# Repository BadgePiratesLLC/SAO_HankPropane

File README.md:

# SAO_HankPropane
HankPropane SAO

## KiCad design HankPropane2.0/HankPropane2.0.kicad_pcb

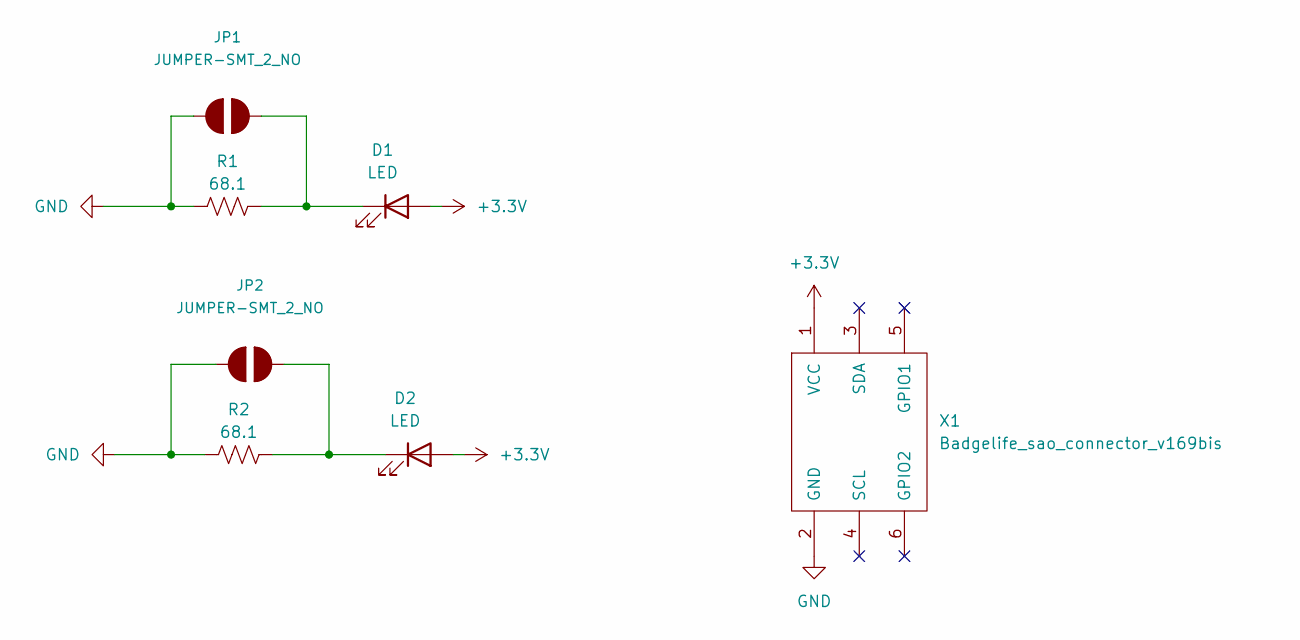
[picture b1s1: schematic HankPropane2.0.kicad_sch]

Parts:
D1, D2: LED; LED_Osram_Lx_P47F_D2mm_ReverseMount_Proper_Mask Only
JP1, JP2: JUMPER-SMT_2_NO; SolderJumper-2_P1.3mm_Open_TrianglePad1.0x1.5mm
R1, R2: 68.1; R_1206_3216Metric_Pad1.30x1.75mm_HandSolder
X1: Badgelife_sao_connector_v169bis; Badgelife-SAOv169-BADGE-2x3_Back

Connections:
+3V3: D1.2 (A), D2.2 (A), X1.1 (VCC)
GND: JP1.1, JP2.1, R1.1, R2.1, X1.2 (GND)
unnamed: D1.1 (K), JP1.2, R1.2
unnamed: D2.1 (K), JP2.2, R2.2

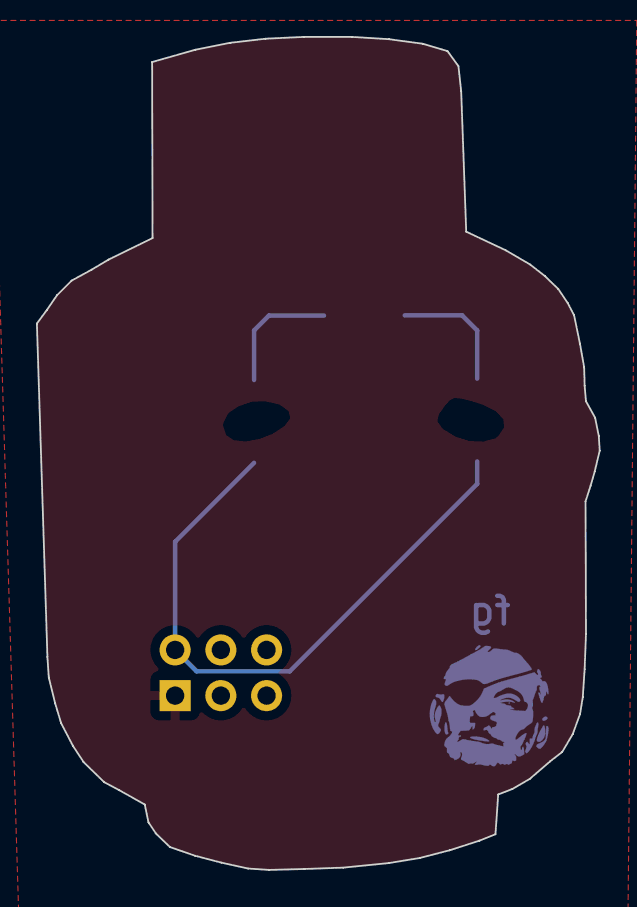
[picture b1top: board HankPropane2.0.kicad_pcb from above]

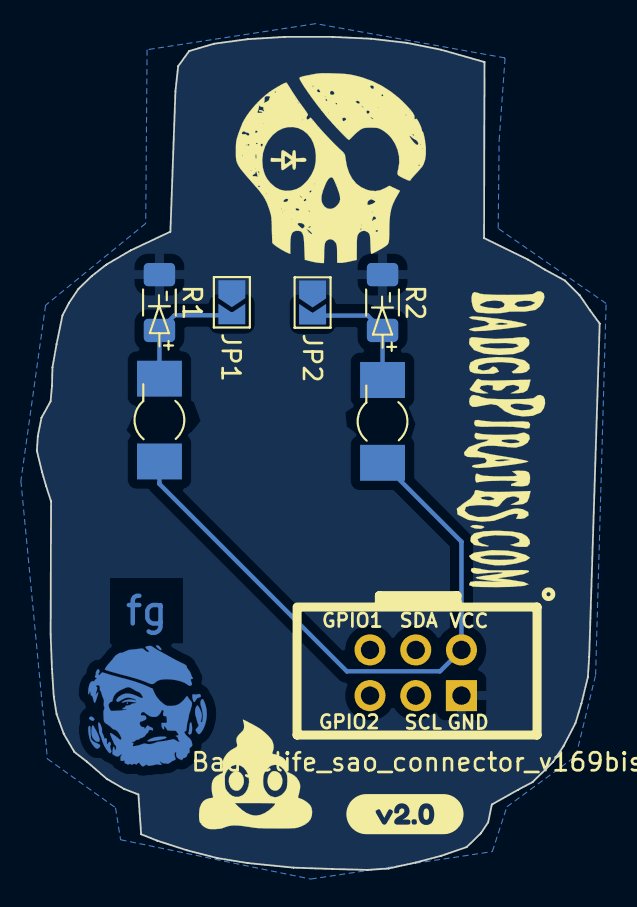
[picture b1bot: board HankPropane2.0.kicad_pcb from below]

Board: 2 copper layers, 31.3 x 46.3 mm, 8 parts (5 on the bottom side), 4 nets.

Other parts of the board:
kibuzzard-62A4E406: G***; kibuzzard-62A4E406

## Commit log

2022-11-23 Add zip files to gitignore
2023-06-19 Added 68.1 ohm current limiting resistors and turbo mode jumpers
2023-06-20 Created new fabrication output files
    Created new fabrication output files for pcbway per https://www.pcbway.com/blog/help_center/How_to_Generate_Gerber_and_Drill_Files_in_KiCad_7_0_ab0d12bb.html
2023-06-20 Changed resistors to 1206
2023-06-21 Minor change
